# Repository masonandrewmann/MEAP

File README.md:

# Mason's ESP32 Audio Prototyping System

MEAP is a hardware and software environment for developing live computer music systems and rapidly prototyping digital electronic instruments.

MEAP's audio library is built as an expansion on top of [Mozzi](https://sensorium.github.io/Mozzi/), implementing extra features that take advantage of the computational power of the ESP32-S3 and improve/simplify the composer's experience.

[Documentation](https://masonmann.online/electronics/meap)

MEAP is used in [MPATE-GE 2047: Advanced Computer Music](https://masonmann.online/2047) at NYU

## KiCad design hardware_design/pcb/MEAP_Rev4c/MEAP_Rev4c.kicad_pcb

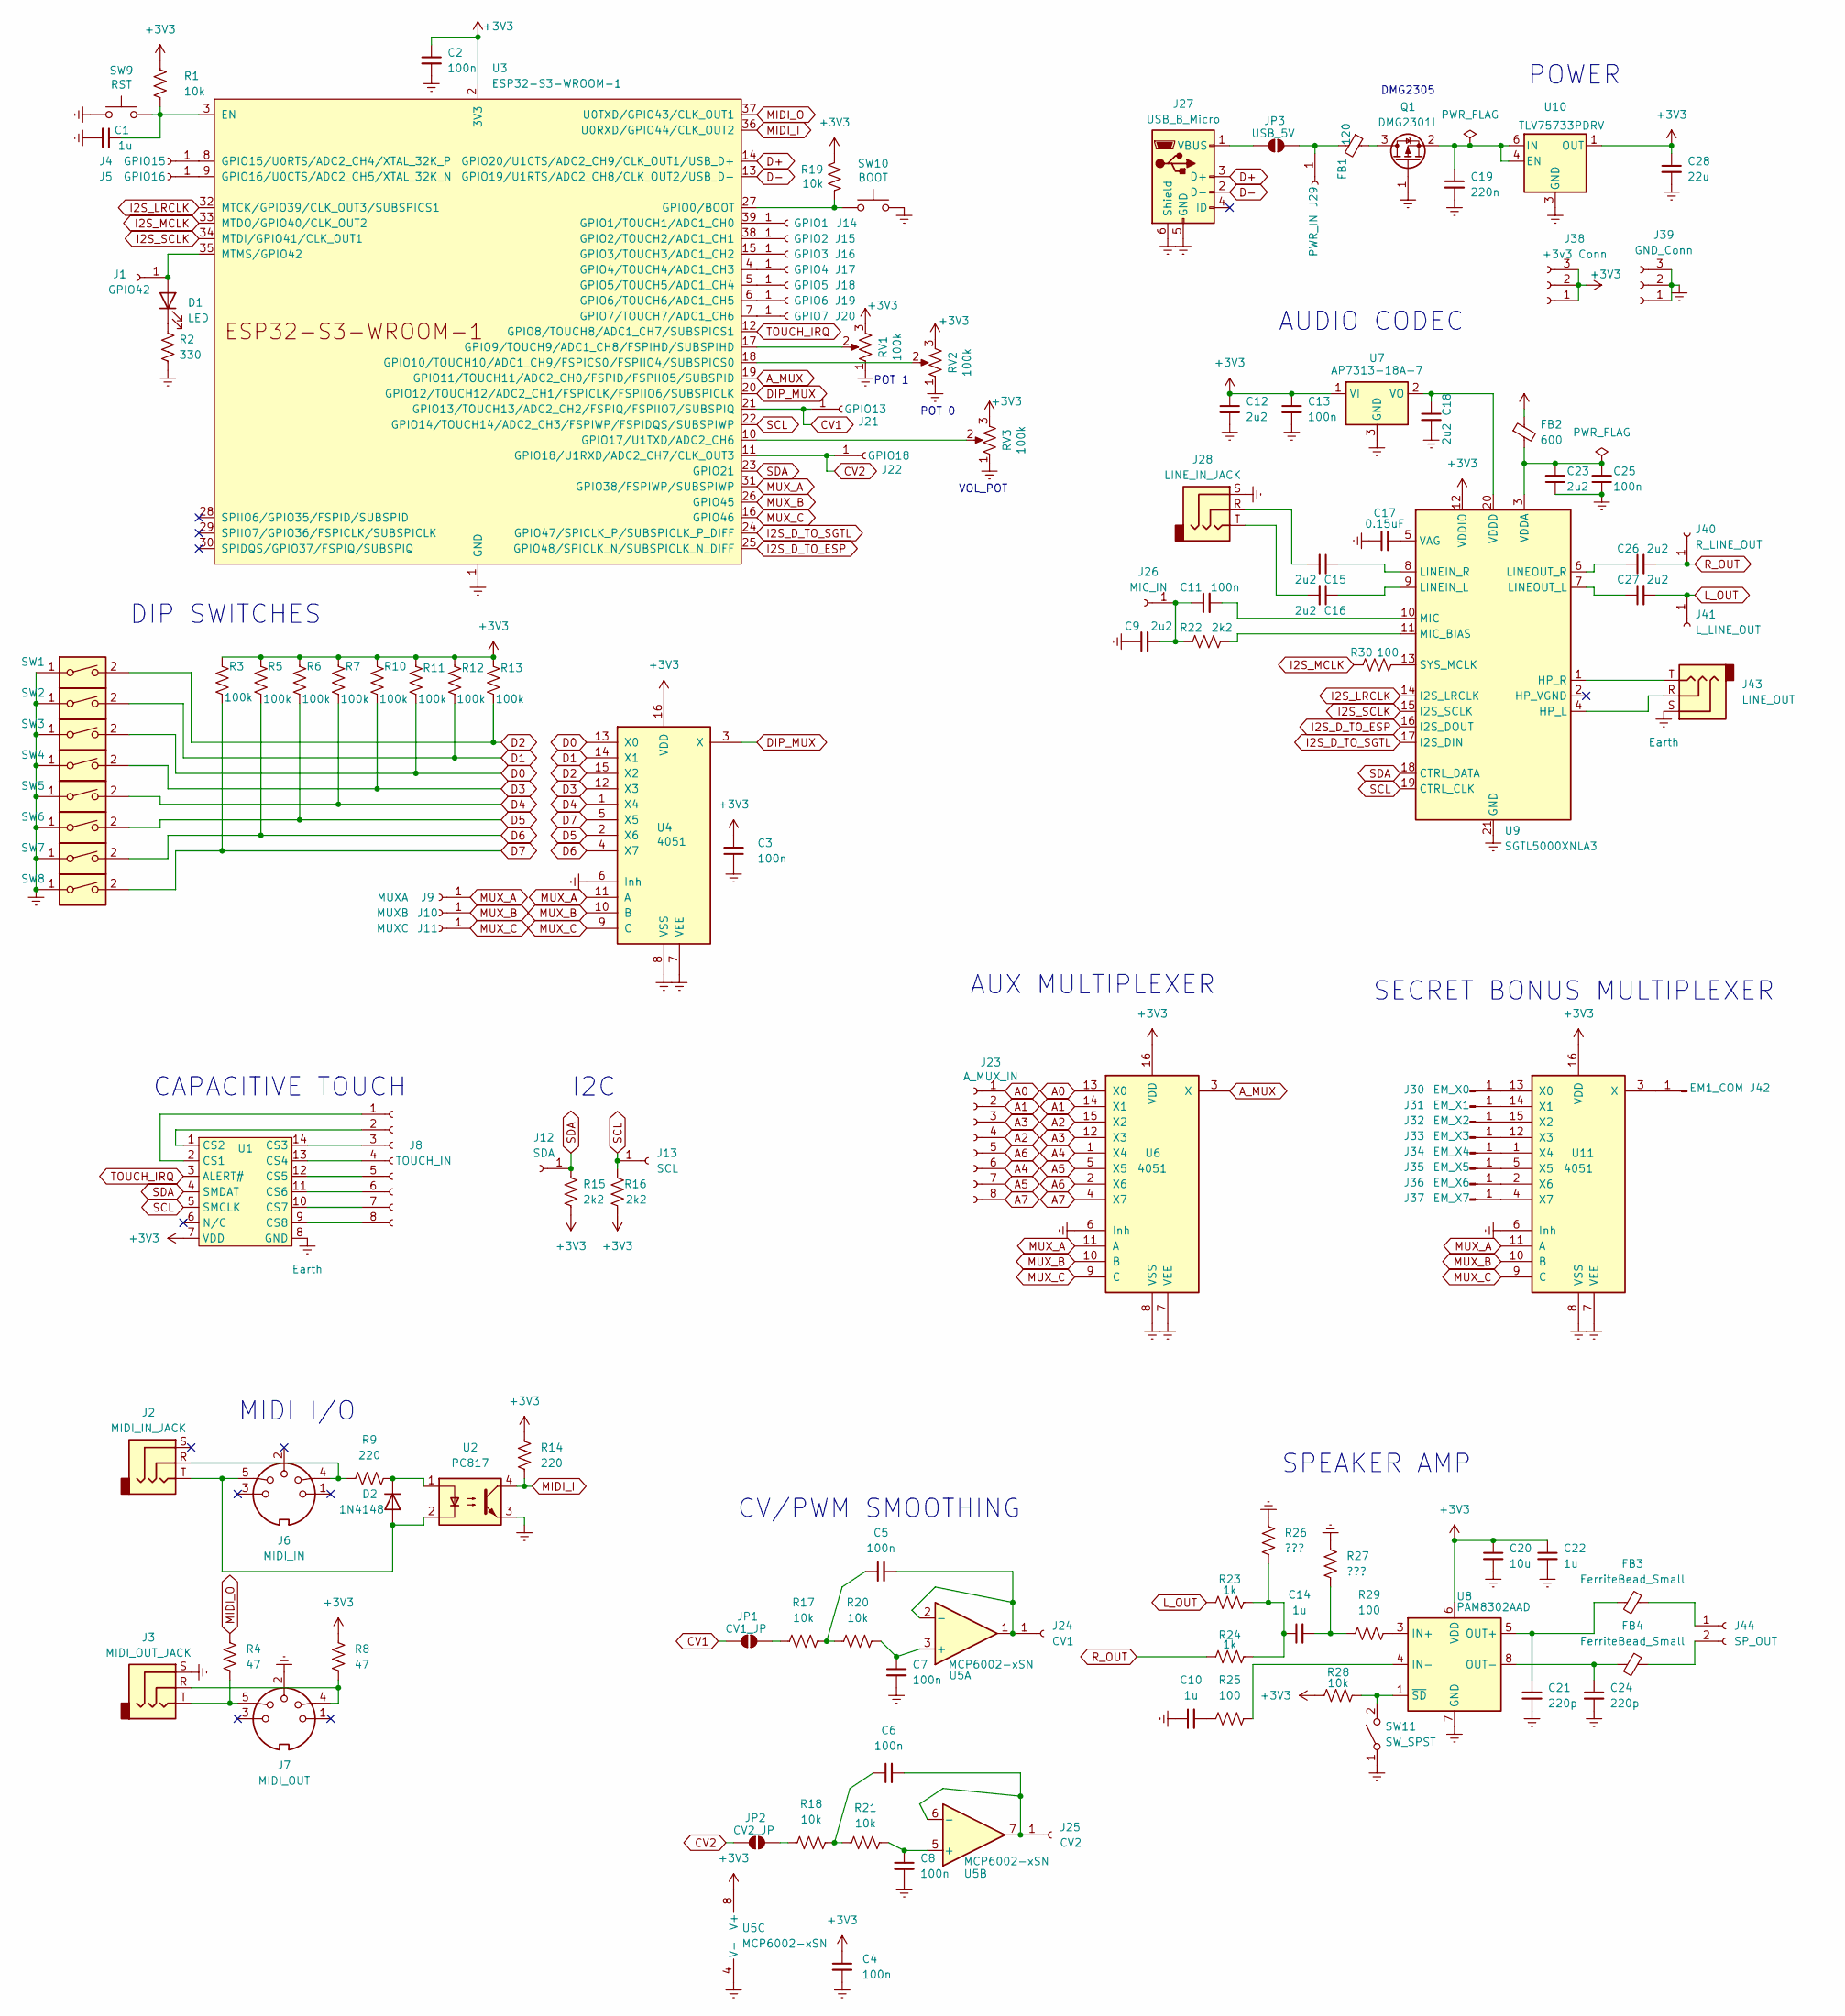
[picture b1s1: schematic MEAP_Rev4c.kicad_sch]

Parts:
C1, C10, C14, C22: 1u; C_0603_1608Metric_Pad1.08x0.95mm_HandSolder
C2, C3, C4, C5, C6, C7, C8, C11, C13, C25: 100n; C_0603_1608Metric_Pad1.08x0.95mm_HandSolder
C9, C12, C15, C16, C18, C23, C26, C27: 2u2; C_0603_1608Metric_Pad1.08x0.95mm_HandSolder
C17: 0.15uF; C_0603_1608Metric_Pad1.08x0.95mm_HandSolder
C19: 220n; C_0603_1608Metric_Pad1.08x0.95mm_HandSolder
C20: 10u; C_0603_1608Metric_Pad1.08x0.95mm_HandSolder
C21, C24: 220p; C_0603_1608Metric_Pad1.08x0.95mm_HandSolder
C28: 22u; C_1210_3225Metric
D1: LED; L_0805_2012Metric_Pad1.05x1.20mm_HandSolder
D2: 1N4148; D_SOD-323
FB1: 120; L_0603_1608Metric
FB2: 600; L_0603_1608Metric
FB3, FB4: FerriteBead_Small; L_0603_1608Metric
J1: GPIO42; Pin_D1.0mm_L10.0mm
J2: MIDI_IN_JACK; Jack_3.5mm_CUI_SJ1-3535NG_Horizontal_NO_FRONT
J3: MIDI_OUT_JACK; Jack_3.5mm_CUI_SJ1-3535NG_Horizontal_NO_FRONT
J4: GPIO15; Pin_D1.0mm_L10.0mm
J5: GPIO16; Pin_D1.0mm_L10.0mm
J6: MIDI_IN
J7: MIDI_OUT
J8: TOUCH_IN; PinHeader_2x04_P2.54mm_Vertical
J9: MUXA; Pin_D1.0mm_L10.0mm
J10: MUXB; Pin_D1.0mm_L10.0mm
J11: MUXC; Pin_D1.0mm_L10.0mm
J12: SDA; Pin_D1.0mm_L10.0mm
J13: SCL; Pin_D1.0mm_L10.0mm
J14: GPIO1; Pin_D1.0mm_L10.0mm
J15: GPIO2; Pin_D1.0mm_L10.0mm
J16: GPIO3; Pin_D1.0mm_L10.0mm
J17: GPIO4; Pin_D1.0mm_L10.0mm
J18: GPIO5; Pin_D1.0mm_L10.0mm
J19: GPIO6; Pin_D1.0mm_L10.0mm
J20: GPIO7; Pin_D1.0mm_L10.0mm
J21: GPIO13; Pin_D1.0mm_L10.0mm
J22: GPIO18; Pin_D1.0mm_L10.0mm
J23: A_MUX_IN; PinHeader_2x04_P2.54mm_Vertical
J24: CV1; Pin_D1.0mm_L10.0mm
J25: CV2; Pin_D1.0mm_L10.0mm
J26: MIC_IN; Pin_D1.0mm_L10.0mm
J27: USB_B_Micro; USB_Micro-B_Molex-105017-0001
J28: LINE_IN_JACK; Jack_3.5mm_CUI_SJ1-3535NG_Horizontal_NO_FRONT
J29: PWR_IN; Pin_D1.0mm_L10.0mm
J30: EM_X0; SolderWirePad_1x01_SMD_1x2mm
J31: EM_X1; SolderWirePad_1x01_SMD_1x2mm
J32: EM_X2; SolderWirePad_1x01_SMD_1x2mm
J33: EM_X3; SolderWirePad_1x01_SMD_1x2mm
J34: EM_X4; SolderWirePad_1x01_SMD_1x2mm
J35: EM_X5; SolderWirePad_1x01_SMD_1x2mm
J36: EM_X6; SolderWirePad_1x01_SMD_1x2mm
J37: EM_X7; SolderWirePad_1x01_SMD_1x2mm
J38: +3v3 Conn; PinHeader_1x03_P2.54mm_Vertical
J39: GND_Conn; PinHeader_1x03_P2.54mm_Vertical
J40: R_LINE_OUT; Pin_D1.0mm_L10.0mm
J41: L_LINE_OUT; Pin_D1.0mm_L10.0mm
J42: EM1_COM; SolderWirePad_1x01_SMD_1x2mm
J43: LINE_OUT; Jack_3.5mm_CUI_SJ1-3535NG_Horizontal_NO_FRONT
J44: SP_OUT; PinHeader_1x02_P2.54mm_Vertical
JP1: CV1_JP; SolderJumper-2_P1.3mm_Open_Pad1.0x1.5mm
JP2: CV2_JP; SolderJumper-2_P1.3mm_Open_Pad1.0x1.5mm
JP3: USB_5V; SolderJumper-2_P1.3mm_Open_Pad1.0x1.5mm
Q1: DMG2301L; SOT-23
R1, R17, R18, R19, R20, R21, R28: 10k; R_0603_1608Metric_Pad0.98x0.95mm_HandSolder
R2: 330; R_0603_1608Metric_Pad0.98x0.95mm_HandSolder
R3, R5, R6, R7, R10, R11, R12, R13: 100k; R_0603_1608Metric_Pad0.98x0.95mm_HandSolder
R4, R8: 47; R_0603_1608Metric_Pad0.98x0.95mm_HandSolder
R9, R14: 220; R_0603_1608Metric_Pad0.98x0.95mm_HandSolder
R15, R16, R22: 2k2; R_0603_1608Metric_Pad0.98x0.95mm_HandSolder
R23, R24: 1k; R_0603_1608Metric_Pad0.98x0.95mm_HandSolder
R25, R29, R30: 100; R_0603_1608Metric_Pad0.98x0.95mm_HandSolder
R26, R27: ???; R_0603_1608Metric_Pad0.98x0.95mm_HandSolder
RV1, RV2, RV3: 100k; PinHeader_1x03_P2.54mm_Vertical
SW1, SW2, SW3, SW4, SW5, SW6, SW7, SW8: SW_DIP_x01; SINGLE_DIP_SWITCH
SW9: RST; SW_Tactile_SPST_NO_Straight_CK_PTS636Sx25SMTRLFS
SW10: BOOT; SW_Tactile_SPST_NO_Straight_CK_PTS636Sx25SMTRLFS
SW11: SW_SPST; SW_Slide_SPDT_Straight_CK_OS102011MS2Q
U1: SOIC-14_3.9x8.7mm_P1.27mm
U2: PC817; DIP-4_W7.62mm
U3: ESP32-S3-WROOM-1; ESP32-S3-WROOM-1U
U4, U6, U11: 4051; SOIC-16_3.9x9.9mm_P1.27mm
U5: MCP6002-xSN; SOIC-8_3.9x4.9mm_P1.27mm
U7: AP7313-18A-7; SOT-23
U8: PAM8302AAD; MSOP-8_3x3mm_P0.65mm
U9: SGTL5000XNLA3; QFN-20-1EP_3x3mm_P0.4mm_EP1.65x1.65mm
U10: TLV75733PDRV; WSON-6-1EP_2x2mm_P0.65mm_EP1x1.6mm

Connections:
+3V3: C2.1, C3.2, C4.1, C12.1, C13.1, C20.1, C22.1, C28.1, FB2.1, J38.1, J38.2, J38.3, R1.1, R3.1, R5.1, R6.1, R7.1, R8.1, R10.1, R11.1, R12.1, R13.1, R14.1, R15.2, R16.2, R19.1, R28.1, RV1.3, RV2.3, RV3.3, U1.7 (VDD), U3.2 (3V3), U4.16 (VDD), U5.8 (V+), U6.16 (VDD), U7.1 (VI), U8.6 (VDD), U9.12 (VDDIO), U10.1 (OUT), U11.16 (VDD)
A0: J23.1, U6.13 (X0)
A1: J23.2, U6.14 (X1)
A2: J23.4, U6.15 (X2)
A3: J23.3, U6.12 (X3)
A4: J23.6, U6.1 (X4)
A5: J23.7, U6.5 (X5)
A6: J23.5, U6.2 (X6)
A7: J23.8, U6.4 (X7)
A_MUX: U3.19 (GPIO11/TOUCH11/ADC2_CH0/FSPID/FSPIIO5/S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), U6.3 (X)
CV1: J21.1, JP1.2 (B), U3.21 (GPIO13/TOUCH13/ADC2_CH2/FSPIQ/FSPIIO7/S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)
CV2: J22.1, JP2.2 (B), U3.11 (GPIO18/U1RXD/ADC2_CH7/CLK_OUT3)
D0: R11.2, SW3.2, U4.13 (X0)
D1: R12.2, SW2.2, U4.14 (X1)
D2: R13.2, SW1.2, U4.15 (X2)
D3: R10.2, SW4.2, U4.12 (X3)
D4: R7.2, SW5.2, U4.1 (X4)
D5: R6.2, SW6.2, U4.2 (X6)
D6: R5.2, SW7.2, U4.4 (X7)
D7: R3.2, SW8.2, U4.5 (X5)
D+: J27.3 (D+), U3.14 (GPIO20/U1CTS/ADC2_CH9/CLK_OUT1/USB_D+)
D-: J27.2 (D-), U3.13 (GPIO19/U1RTS/ADC2_CH8/CLK_OUT2/USB_D-)
DIP_MUX: U3.20 (GPIO12/TOUCH12/ADC2_CH1/FSPICLK/FSPIIO6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), U4.3 (X)
Earth: C1.2, C2.2, C3.1, C4.2, C7.2, C8.2, C9.1, C10.1, C12.2, C13.2, C17.1, C18.2, C19.2, C20.2, C21.2, C22.2, C23.1, C24.2, C25.1, C28.2, J3.S, J7.2, J27.5 (GND), J27.6 (Shield), J28.S, J39.1, J39.2, J39.3, J43.S, Q1.1 (G), R2.2, R26.2, R27.2, RV1.1, RV2.1, RV3.1, SW1.1, SW2.1, SW3.1, SW4.1, SW5.1, SW6.1, SW7.1, SW8.1, SW9.1, SW10.2, SW11.1 (A), U1.8 (GND), U2.3, U3.1 (GND), U3.40 (GND), U3.41 (GND), U4.6 (Inh), U4.7 (VEE), U4.8 (VSS), U5.4 (V-), U6.6 (Inh), U6.7 (VEE), U6.8 (VSS), U7.3 (GND), U8.7 (GND), U9.21 (GND), U10.3 (GND), U10.7 (GND), U11.6 (Inh), U11.7 (VEE), U11.8 (VSS)
I2S_D_TO_ESP: U3.25 (GPIO48/SPICLK_N/SUBSPICLK_N_DIFF), U9.16 (I2S_DOUT)
I2S_D_TO_SGTL: U3.24 (GPIO47/SPICLK_P/SUBSPICLK_P_DIFF), U9.17 (I2S_DIN)
I2S_LRCLK: U3.32 (MTCK/GPIO39/CLK_OUT3/SUBSPICS1), U9.14 (I2S_LRCLK)
I2S_MCLK: R30.1, U3.33 (MTDO/GPIO40/CLK_OUT2)
I2S_SCLK: U3.34 (MTDI/GPIO41/CLK_OUT1), U9.15 (I2S_SCLK)
L_OUT: C27.2, J41.1, R23.1
MIDI_I: R14.2, U2.4, U3.36 (U0RXD/GPIO44/CLK_OUT2)
MIDI_O: R4.1, U3.37 (U0TXD/GPIO43/CLK_OUT1)
MUX_A: J9.1, U3.31 (GPIO38/FSPIWP/SUBSPIWP), U4.11 (A), U6.11 (A), U11.11 (A)
MUX_B: J10.1, U3.26 (GPIO45), U4.10 (B), U6.10 (B), U11.10 (B)
MUX_C: J11.1, U3.16 (GPIO46), U4.9 (C), U6.9 (C), U11.9 (C)
unnamed: C5.1, R17.2, R20.1
unnamed: C6.1, R18.2, R21.1
unnamed: C10.2, R25.1
unnamed: C14.1, R23.2, R24.2, R26.1
unnamed: C14.2, R27.1, R29.1
unnamed: C15.2, J28.R
unnamed: C16.2, J28.T
unnamed: D1.2 (A), J1.1, U3.35 (MTMS/GPIO42)
unnamed: D1.1 (K), R2.1
unnamed: D2.2 (A), J2.T, J6.5, U2.2
unnamed: D2.1 (K), R9.2, U2.1
unnamed: J2.R, J6.4, R9.1
unnamed: J3.R, J7.4, R8.2
unnamed: J3.T, J7.5, R4.2
unnamed: J4.1, U3.8 (GPIO15/U0RTS/ADC2_CH4/XTAL_32K_P)
unnamed: J5.1, U3.9 (GPIO16/U0CTS/ADC2_CH5/XTAL_32K_N)
unnamed: J8.1, U1.2 (CS1)
unnamed: J8.2, U1.1 (CS2)
unnamed: J8.3, U1.14 (CS3)
unnamed: J8.4, U1.13 (CS4)
unnamed: J8.5, U1.12 (CS5)
unnamed: J8.6, U1.11 (CS6)
unnamed: J8.7, U1.10 (CS7)
unnamed: J8.8, U1.9 (CS8)
unnamed: J14.1, U3.39 (GPIO1/TOUCH1/ADC1_CH0)
unnamed: J15.1, U3.38 (GPIO2/TOUCH2/ADC1_CH1)
unnamed: J16.1, U3.15 (GPIO3/TOUCH3/ADC1_CH2)
unnamed: J17.1, U3.4 (GPIO4/TOUCH4/ADC1_CH3)
unnamed: J18.1, U3.5 (GPIO5/TOUCH5/ADC1_CH4)
unnamed: J19.1, U3.6 (GPIO6/TOUCH6/ADC1_CH5)
unnamed: J20.1, U3.7 (GPIO7/TOUCH7/ADC1_CH6)
unnamed: C5.2, J24.1, U5.1, U5.2 (-)
unnamed: C6.2, J25.1, U5.6 (-), U5.7
unnamed: C9.2, C11.1, J26.1, R22.1
unnamed: J27.1 (VBUS), JP3.2 (B)
unnamed: FB1.2, J29.1, JP3.1 (A)
unnamed: J30.1, U11.13 (X0)
unnamed: J31.1, U11.14 (X1)
unnamed: J32.1, U11.15 (X2)
unnamed: J33.1, U11.12 (X3)
unnamed: J34.1, U11.1 (X4)
unnamed: J35.1, U11.5 (X5)
unnamed: J36.1, U11.2 (X6)
unnamed: J37.1, U11.4 (X7)
unnamed: J42.1, U11.3 (X)
unnamed: FB3.2, J44.1
unnamed: FB4.2, J44.2
unnamed: JP1.1 (A), R17.1
unnamed: JP2.1 (A), R18.1
unnamed: FB1.1, Q1.3 (D)
unnamed: C19.1, Q1.2 (S), U10.4 (EN), U10.6 (IN)
unnamed: R28.2, SW11.2 (B), U8.1 (~SD)
unnamed: C1.1, R1.2, SW9.2, U3.3 (EN)
unnamed: R19.2, SW10.1, U3.27 (GPIO0/BOOT)
unnamed: RV1.2, U3.17 (GPIO9/TOUCH9/ADC1_CH8/FSPIHD/SUBSPIHD)
unnamed: RV2.2, U3.18 (GPIO10/TOUCH10/ADC1_CH9/FSPICS0/FSPIIO4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)
unnamed: RV3.2, U3.10 (GPIO17/U1TXD/ADC2_CH6)
unnamed: C7.1, R20.2, U5.3 (+)
unnamed: C8.1, R21.2, U5.5 (+)
unnamed: C18.1, U7.2 (VO), U9.20 (VDDD)
unnamed: R29.2, U8.3 (IN+)
unnamed: R25.2, U8.4 (IN-)
unnamed: C21.1, FB3.1, U8.5 (OUT+)
unnamed: C24.1, FB4.1, U8.8 (OUT-)
unnamed: J43.R, U9.4 (HP_L)
unnamed: J43.T, U9.1 (HP_R)
unnamed: C16.1, U9.9 (LINEIN_L)
unnamed: C15.1, U9.8 (LINEIN_R)
unnamed: C27.1, U9.7 (LINEOUT_L)
unnamed: C26.1, U9.6 (LINEOUT_R)
unnamed: C11.2, U9.10 (MIC)
unnamed: R22.2, U9.11 (MIC_BIAS)
unnamed: R30.2, U9.13 (SYS_MCLK)
unnamed: C17.2, U9.5 (VAG)
unnamed: C23.2, C25.2, FB2.2, U9.3 (VDDA)
R_OUT: C26.2, J40.1, R24.1
SCL: J13.1, R16.1, U1.5 (SMCLK), U3.22 (GPIO14/TOUCH14/ADC2_CH3/FSPIWP/FSPIDQS/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), U9.19 (CTRL_CLK)
SDA: J12.1, R15.1, U1.4 (SMDAT), U3.23 (GPIO21), U9.18 (CTRL_DATA)
TOUCH_IRQ: U1.3 (ALERT#), U3.12 (GPIO8/TOUCH8/ADC1_CH7/SUBSPICS1)

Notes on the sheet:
CV/PWM SMOOTHING
POWER
VOL_POT
POT 0
AUX MULTIPLEXER
I2C
DMG2305
POT 1
SPEAKER AMP
DIP SWITCHES
MIDI I/O
SECRET BONUS MULTIPLEXER
CAPACITIVE TOUCH
AUDIO CODEC

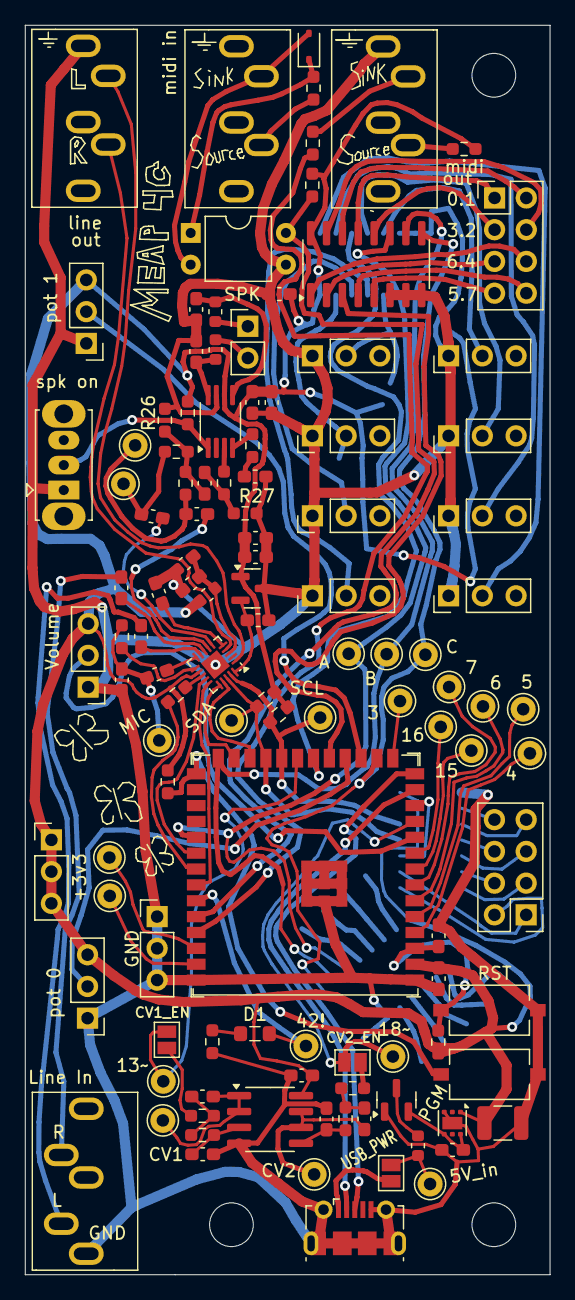
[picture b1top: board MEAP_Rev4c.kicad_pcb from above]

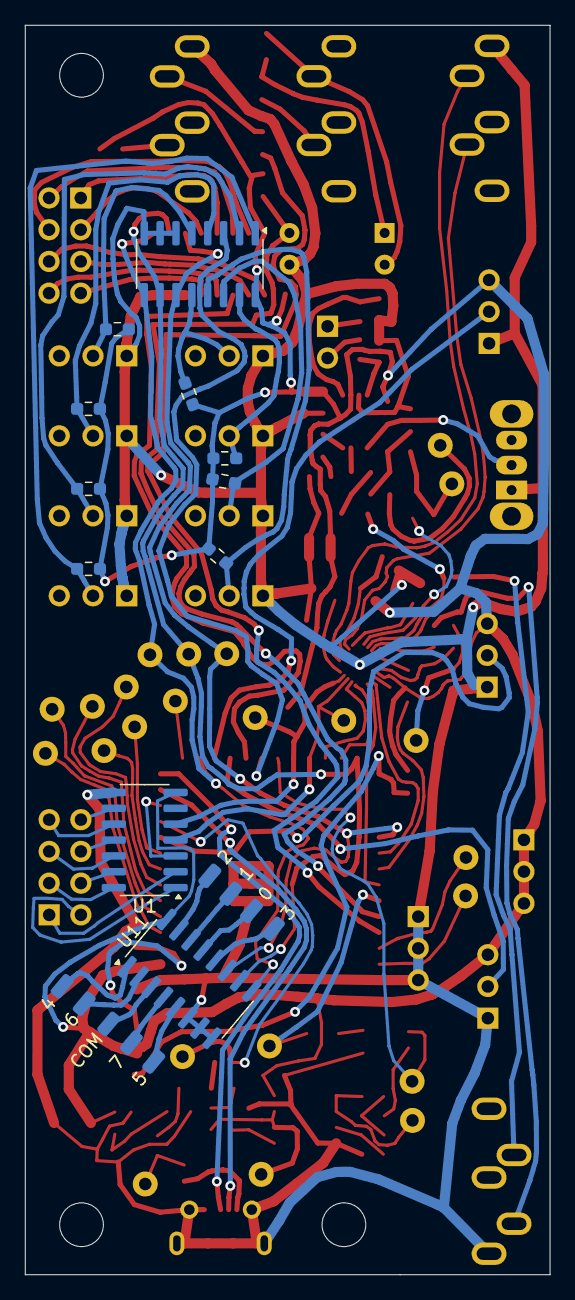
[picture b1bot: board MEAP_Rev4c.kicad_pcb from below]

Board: 2 copper layers, 42.0 x 100.0 mm, 135 parts (20 on the bottom side), 114 nets.

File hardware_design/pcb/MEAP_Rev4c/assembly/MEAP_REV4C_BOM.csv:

"Reference","Value","Footprint","Qty","DNP"
"U10","TLV75733PDRV","Package_SON:WSON-6-1EP_2x2mm_P0.65mm_EP1x1.6mm","1",""
"U9","SGTL5000XNLA3","Package_DFN_QFN:QFN-20-1EP_3x3mm_P0.4mm_EP1.65x1.65mm","1",""
"U8","PAM8302AAD","Package_SO:MSOP-8_3x3mm_P0.65mm","1",""
"U7","AP7313-18A-7","Package_TO_SOT_SMD:SOT-23","1",""
"U5","MCP6002-xSN","Package_SO:SOIC-8_3.9x4.9mm_P1.27mm","1",""
"U4,U6,U11","4051","Package_SO:SOIC-16_3.9x9.9mm_P1.27mm","3",""
"U3","ESP32-S3-WROOM-1","PCM_Espressif:ESP32-S3-WROOM-1U","1",""
"U2","PC817","Package_DIP:DIP-4_W7.62mm","1",""
"U1","~","Package_SO:SOIC-14_3.9x8.7mm_P1.27mm","1",""
"SW11","SW_SPST","Button_Switch_THT:SW_Slide_SPDT_Straight_CK_OS102011MS2Q","1",""
"SW10","BOOT","Button_Switch_SMD:SW_Tactile_SPST_NO_Straight_CK_PTS636Sx25SMTRLFS","1",""
"SW9","RST","Button_Switch_SMD:SW_Tactile_SPST_NO_Straight_CK_PTS636Sx25SMTRLFS","1",""
"SW1,SW2,SW3,SW4,SW5,SW6,SW7,SW8","SW_DIP_x01","mason_parts:SINGLE_DIP_SWITCH","8",""
"RV1,RV2,RV3","100k","Connector_PinHeader_2.54mm:PinHeader_1x03_P2.54mm_Vertical","3",""
"R26,R27","???","Resistor_SMD:R_0603_1608Metric_Pad0.98x0.95mm_HandSolder","2",""
"R25,R29,R30","100","Resistor_SMD:R_0603_1608Metric_Pad0.98x0.95mm_HandSolder","3",""
"R23,R24","1k","Resistor_SMD:R_0603_1608Metric_Pad0.98x0.95mm_HandSolder","2",""
"R15,R16,R22","2k2","Resistor_SMD:R_0603_1608Metric_Pad0.98x0.95mm_HandSolder","3",""
"R9,R14","220","Resistor_SMD:R_0603_1608Metric_Pad0.98x0.95mm_HandSolder","2",""
"R4,R8","47","Resistor_SMD:R_0603_1608Metric_Pad0.98x0.95mm_HandSolder","2",""
"R3,R5,R6,R7,R10,R11,R12,R13","100k","Resistor_SMD:R_0603_1608Metric_Pad0.98x0.95mm_HandSolder","8",""
"R2","330","Resistor_SMD:R_0603_1608Metric_Pad0.98x0.95mm_HandSolder","1",""
"R1,R17,R18,R19,R20,R21,R28","10k","Resistor_SMD:R_0603_1608Metric_Pad0.98x0.95mm_HandSolder","7",""
"Q1","DMG2301L","Package_TO_SOT_SMD:SOT-23","1",""
"J44","SP_OUT","Connector_PinHeader_2.54mm:PinHeader_1x02_P2.54mm_Vertical","1",""
"J43","LINE_OUT","mason_parts:Jack_3.5mm_CUI_SJ1-3535NG_Horizontal_NO_FRONT","1",""
"J42","EM1_COM","Connector_Wire:SolderWirePad_1x01_SMD_1x2mm","1",""
"J41","L_LINE_OUT","Connector_Pin:Pin_D1.0mm_L10.0mm","1",""
"J40","R_LINE_OUT","Connector_Pin:Pin_D1.0mm_L10.0mm","1",""
"J39","GND_Conn","Connector_PinHeader_2.54mm:PinHeader_1x03_P2.54mm_Vertical","1",""
"J38","+3v3 Conn","Connector_PinHeader_2.54mm:PinHeader_1x03_P2.54mm_Vertical","1",""
"J37","EM_X7","Connector_Wire:SolderWirePad_1x01_SMD_1x2mm","1",""
"J36","EM_X6","Connector_Wire:SolderWirePad_1x01_SMD_1x2mm","1",""
"J35","EM_X5","Connector_Wire:SolderWirePad_1x01_SMD_1x2mm","1",""
"J34","EM_X4","Connector_Wire:SolderWirePad_1x01_SMD_1x2mm","1",""
"J33","EM_X3","Connector_Wire:SolderWirePad_1x01_SMD_1x2mm","1",""
"J32","EM_X2","Connector_Wire:SolderWirePad_1x01_SMD_1x2mm","1",""
"J31","EM_X1","Connector_Wire:SolderWirePad_1x01_SMD_1x2mm","1",""
"J30","EM_X0","Connector_Wire:SolderWirePad_1x01_SMD_1x2mm","1",""
"J29","PWR_IN","Connector_Pin:Pin_D1.0mm_L10.0mm","1",""
"J28","LINE_IN_JACK","mason_parts:Jack_3.5mm_CUI_SJ1-3535NG_Horizontal_NO_FRONT","1",""
"J27","USB_B_Micro","Connector_USB:USB_Micro-B_Molex-105017-0001","1",""
"J26","MIC_IN","Connector_Pin:Pin_D1.0mm_L10.0mm","1",""
"J25","CV2","Connector_Pin:Pin_D1.0mm_L10.0mm","1",""
"J24","CV1","Connector_Pin:Pin_D1.0mm_L10.0mm","1",""
"J23","A_MUX_IN","Connector_PinHeader_2.54mm:PinHeader_2x04_P2.54mm_Vertical","1",""
"J22","GPIO18","Connector_Pin:Pin_D1.0mm_L10.0mm","1",""
"J21","GPIO13","Connector_Pin:Pin_D1.0mm_L10.0mm","1",""
"J20","GPIO7","Connector_Pin:Pin_D1.0mm_L10.0mm","1",""
"J19","GPIO6","Connector_Pin:Pin_D1.0mm_L10.0mm","1",""
"J18","GPIO5","Connector_Pin:Pin_D1.0mm_L10.0mm","1",""
"J17","GPIO4","Connector_Pin:Pin_D1.0mm_L10.0mm","1",""
"J16","GPIO3","Connector_Pin:Pin_D1.0mm_L10.0mm","1",""
"J15","GPIO2","Connector_Pin:Pin_D1.0mm_L10.0mm","1",""
"J14","GPIO1","Connector_Pin:Pin_D1.0mm_L10.0mm","1",""
"J13","SCL","Connector_Pin:Pin_D1.0mm_L10.0mm","1",""
"J12","SDA","Connector_Pin:Pin_D1.0mm_L10.0mm","1",""
"J11","MUXC","Connector_Pin:Pin_D1.0mm_L10.0mm","1",""
"J10","MUXB","Connector_Pin:Pin_D1.0mm_L10.0mm","1",""
"J9","MUXA","Connector_Pin:Pin_D1.0mm_L10.0mm","1",""
"J8","TOUCH_IN","Connector_PinHeader_2.54mm:PinHeader_2x04_P2.54mm_Vertical","1",""
"J7","MIDI_OUT","","1",""
"J6","MIDI_IN","","1",""
"J5","GPIO16","Connector_Pin:Pin_D1.0mm_L10.0mm","1",""
"J4","GPIO15","Connector_Pin:Pin_D1.0mm_L10.0mm","1",""
"J3","MIDI_OUT_JACK","mason_parts:Jack_3.5mm_CUI_SJ1-3535NG_Horizontal_NO_FRONT","1",""
"J2","MIDI_IN_JACK","mason_parts:Jack_3.5mm_CUI_SJ1-3535NG_Horizontal_NO_FRONT","1",""
"J1","GPIO42","Connector_Pin:Pin_D1.0mm_L10.0mm","1",""
"FB3,FB4","FerriteBead_Small","Inductor_SMD:L_0603_1608Metric","2",""
"FB2","600","Inductor_SMD:L_0603_1608Metric","1",""
"FB1","120","Inductor_SMD:L_0603_1608Metric","1",""
"D2","1N4148","Diode_SMD:D_SOD-323","1",""
"D1","LED","Inductor_SMD:L_0805_2012Metric_Pad1.05x1.20mm_HandSolder","1",""
"C28","22u","Capacitor_SMD:C_1210_3225Metric","1",""
"C21,C24","220p","Capacitor_SMD:C_0603_1608Metric_Pad1.08x0.95mm_HandSolder","2",""
"C20","10u","Capacitor_SMD:C_0603_1608Metric_Pad1.08x0.95mm_HandSolder","1",""
"C19","220n","Capacitor_SMD:C_0603_1608Metric_Pad1.08x0.95mm_HandSolder","1",""
"C17","0.15uF","Capacitor_SMD:C_0603_1608Metric_Pad1.08x0.95mm_HandSolder","1",""
"C9,C12,C15,C16,C18,C23,C26,C27","2u2","Capacitor_SMD:C_0603_1608Metric_Pad1.08x0.95mm_HandSolder","8",""
"C2,C3,C4,C5,C6,C7,C8,C11,C13,C25","100n","Capacitor_SMD:C_0603_1608Metric_Pad1.08x0.95mm_HandSolder","10",""
"C1,C10,C14,C22","1u","Capacitor_SMD:C_0603_1608Metric_Pad1.08x0.95mm_HandSolder","4",""

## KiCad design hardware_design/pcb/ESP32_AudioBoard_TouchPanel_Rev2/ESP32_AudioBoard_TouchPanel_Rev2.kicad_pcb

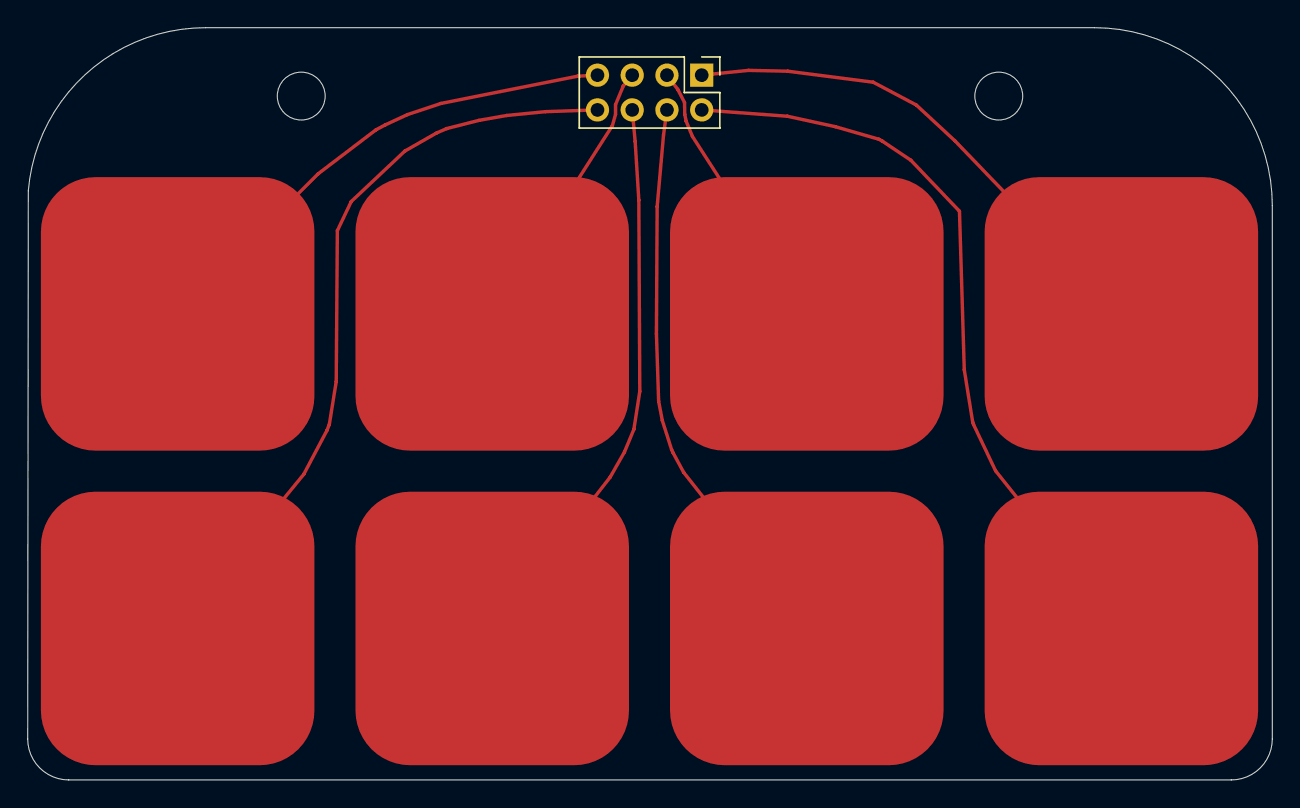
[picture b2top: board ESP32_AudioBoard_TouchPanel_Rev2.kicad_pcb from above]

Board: 2 copper layers, 91.0 x 55.0 mm, 9 parts (0 on the bottom side), 8 nets.

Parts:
J1: Conn_01x08_Female; PinHeader_2x04_P2.54mm_Vertical
J2: Pad #0; TouchPad
J3: Pad #1; TouchPad
J4: Pad #2; TouchPad
J5: Pad #3; TouchPad
J6: Pad #4; TouchPad
J7: Pad #5; TouchPad
J8: Pad #6; TouchPad
J9: Pad #7; TouchPad

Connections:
unnamed: J1.1, J8.1
unnamed: J1.2, J9.1
unnamed: J1.3, J6.1
unnamed: J1.4, J7.1
unnamed: J1.5, J4.1
unnamed: J1.6, J5.1
unnamed: J1.7, J2.1
unnamed: J1.8, J3.1
